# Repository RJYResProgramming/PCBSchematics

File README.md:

# PCBSchematics
Schematics and Board Layouts for PCBs

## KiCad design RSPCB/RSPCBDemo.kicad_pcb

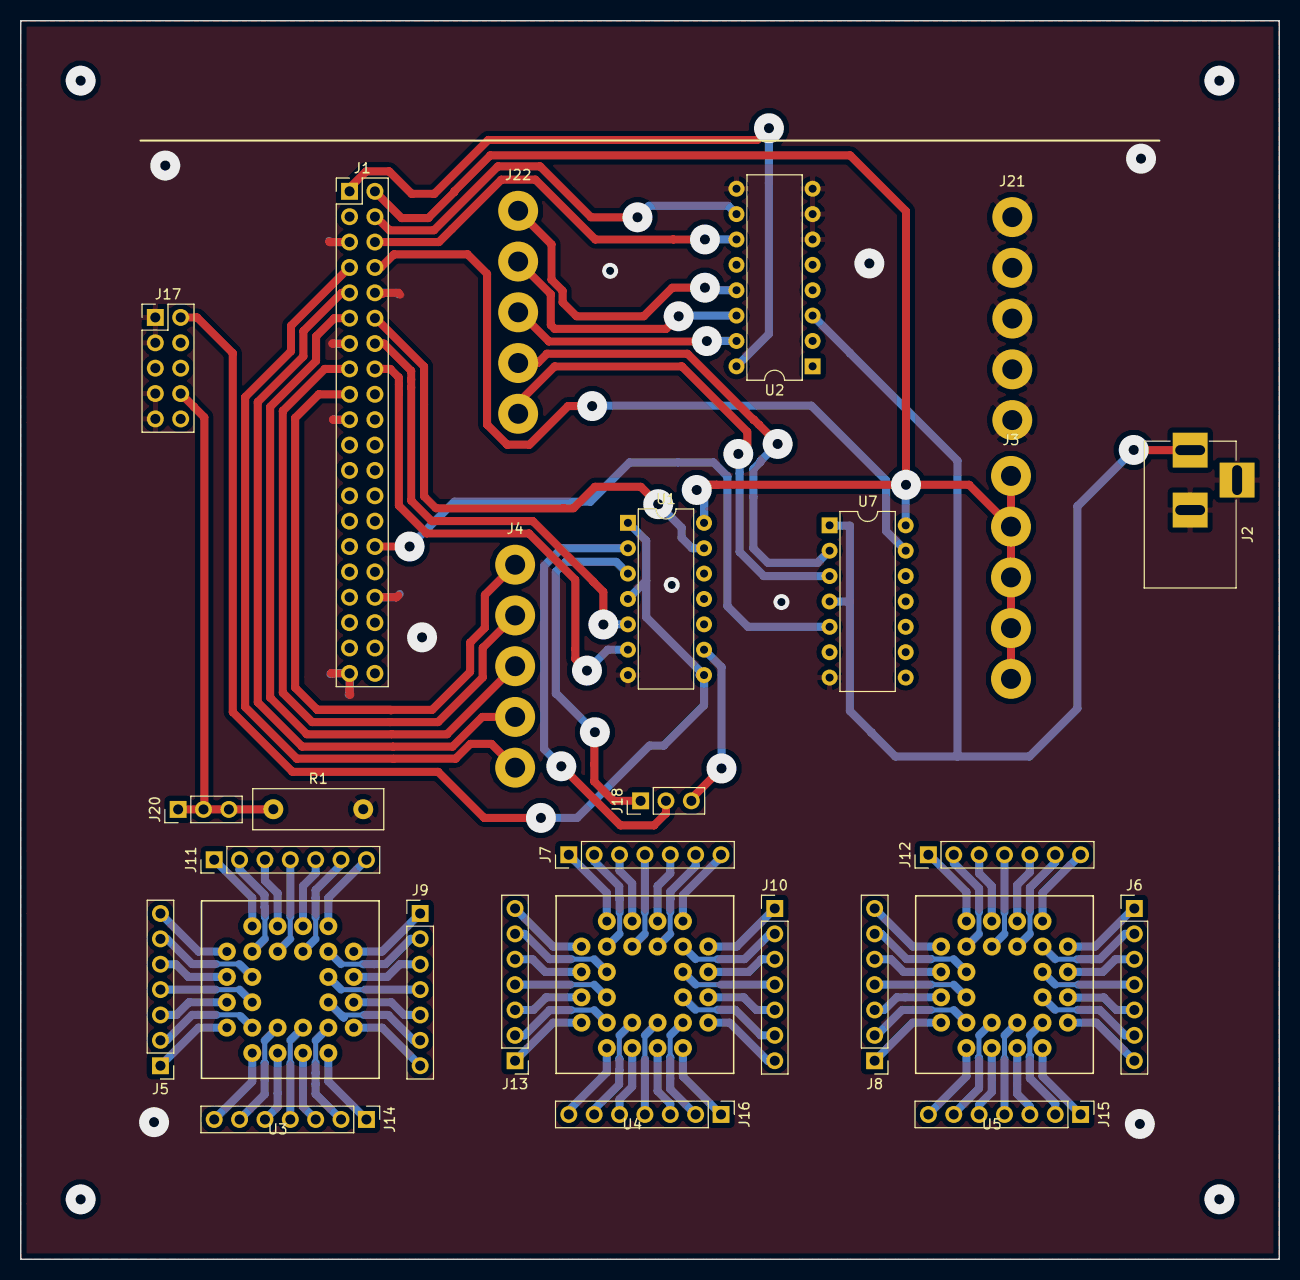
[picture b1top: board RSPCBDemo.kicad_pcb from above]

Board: 2 copper layers, 126.0 x 124.0 mm, 28 parts (0 on the bottom side), 110 nets.

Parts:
J1: CONN_02X20; Pin_Header_Straight_2x20_Pitch2.54mm
J2: BARREL_JACK
J3, J4, J21, J22: CONN_01X05; Pin_Header_Straight_1x05_Pitch5.08mm(Large)
J5, J6, J7, J8, J9, J10, J11, J12, J13, J14, J15, J16: CONN_01X07; Pin_Header_Straight_1x07_Pitch2.54mm
J17: CONN_02X05; Pin_Header_Straight_2x05_Pitch2.54mm
J18, J20: CONN_01X03; Pin_Header_Straight_1x03_Pitch2.54mm
R1: R; R_Box_L13.0mm_W4.0mm_P9.00mm
U1, U7: 4066; DIP-14_W7.62mm
U2: 4051; DIP-16_W7.62mm
U3, U4, U5: 28PinPLCCSocket

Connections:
3.3V: J1.2, J3.1, J3.2, J3.3, J3.4, J3.5, U1.14, U7.14
5V: J1.1, U2.16
BUTTON1: J1.11, J4.3
BUTTON2: J1.15, J4.2
BUTTON3: J1.17, J4.1
GND: J1.5, J1.10, J1.13, J1.19, J1.34, J1.39, J2.2, J2.3, J17.1, J17.3, J17.7, J17.9, J21.1, J21.2, J21.3, J21.4, J21.5, R1.2, U1.7, U2.6, U2.7, U2.8, U2.9, U7.7
GO: J1.7, J4.5
GO_LED: J1.8, U7.13
GO_LEDOut: J22.4, U7.2
HOLD: J1.9, J4.4
HOLD_LED: J1.30, U7.5
HOLD_LEDOut: J22.5, U7.3
IN1: J17.2, U1.1, U1.4, U1.8
LED1: J22.1, U2.13
LED2: J22.2, U2.14
LED3: J22.3, U2.15
LED_PowerIn: J2.1, U2.3, U7.1, U7.4
MUXA: J1.6, U2.11
MUXB: J1.4, U2.10
unnamed: J5.1, U3.11
unnamed: J5.2, U3.10
unnamed: J5.3, U3.9
unnamed: J5.4, U3.8
unnamed: J5.5, U3.7
unnamed: J5.6, U3.6
unnamed: J5.7, U3.5
unnamed: J6.1, U5.25
unnamed: J6.2, U5.24
unnamed: J6.3, U5.23
unnamed: J6.4, U5.22
unnamed: J6.5, U5.21
unnamed: J6.6, U5.20
unnamed: J6.7, U5.19
unnamed: J7.1, U4.4
unnamed: J7.2, U4.3
unnamed: J7.3, U4.2
unnamed: J7.4, U4.1
unnamed: J7.5, U4.28
unnamed: J7.6, U4.27
unnamed: J7.7, U4.26
unnamed: J8.1, U5.11
unnamed: J8.2, U5.10
unnamed: J8.3, U5.9
unnamed: J8.4, U5.8
unnamed: J8.5, U5.7
unnamed: J8.6, U5.6
unnamed: J8.7, U5.5
unnamed: J9.1, U3.25
unnamed: J9.2, U3.24
unnamed: J9.3, U3.23
unnamed: J9.4, U3.22
unnamed: J9.5, U3.21
unnamed: J9.6, U3.20
unnamed: J9.7, U3.19
unnamed: J10.1, U4.25
unnamed: J10.2, U4.24
unnamed: J10.3, U4.23
unnamed: J10.4, U4.22
unnamed: J10.5, U4.21
unnamed: J10.6, U4.20
unnamed: J10.7, U4.19
unnamed: J11.1, U3.4
unnamed: J11.2, U3.3
unnamed: J11.3, U3.2
unnamed: J11.4, U3.1
unnamed: J11.5, U3.28
unnamed: J11.6, U3.27
unnamed: J11.7, U3.26
unnamed: J12.1, U5.4
unnamed: J12.2, U5.3
unnamed: J12.3, U5.2
unnamed: J12.4, U5.1
unnamed: J12.5, U5.28
unnamed: J12.6, U5.27
unnamed: J12.7, U5.26
unnamed: J13.1, U4.11
unnamed: J13.2, U4.10
unnamed: J13.3, U4.9
unnamed: J13.4, U4.8
unnamed: J13.5, U4.7
unnamed: J13.6, U4.6
unnamed: J13.7, U4.5
unnamed: J14.1, U3.18
unnamed: J14.2, U3.17
unnamed: J14.3, U3.16
unnamed: J14.4, U3.15
unnamed: J14.5, U3.14
unnamed: J14.6, U3.13
unnamed: J14.7, U3.12
unnamed: J15.1, U5.18
unnamed: J15.2, U5.17
unnamed: J15.3, U5.16
unnamed: J15.4, U5.15
unnamed: J15.5, U5.14
unnamed: J15.6, U5.13
unnamed: J15.7, U5.12
unnamed: J16.1, U4.18
unnamed: J16.2, U4.17
unnamed: J16.3, U4.16
unnamed: J16.4, U4.15
unnamed: J16.5, U4.14
unnamed: J16.6, U4.13
unnamed: J16.7, U4.12
O1: J17.8, J20.1, J20.2, J20.3, R1.1
QUAD1: J1.12, U1.13
QUAD2: J1.14, U1.5
QUAD3: J1.16, U1.6
RTD1: J18.2, U1.2
RTD2: J18.1, U1.3
RTD3: J18.3, U1.9
